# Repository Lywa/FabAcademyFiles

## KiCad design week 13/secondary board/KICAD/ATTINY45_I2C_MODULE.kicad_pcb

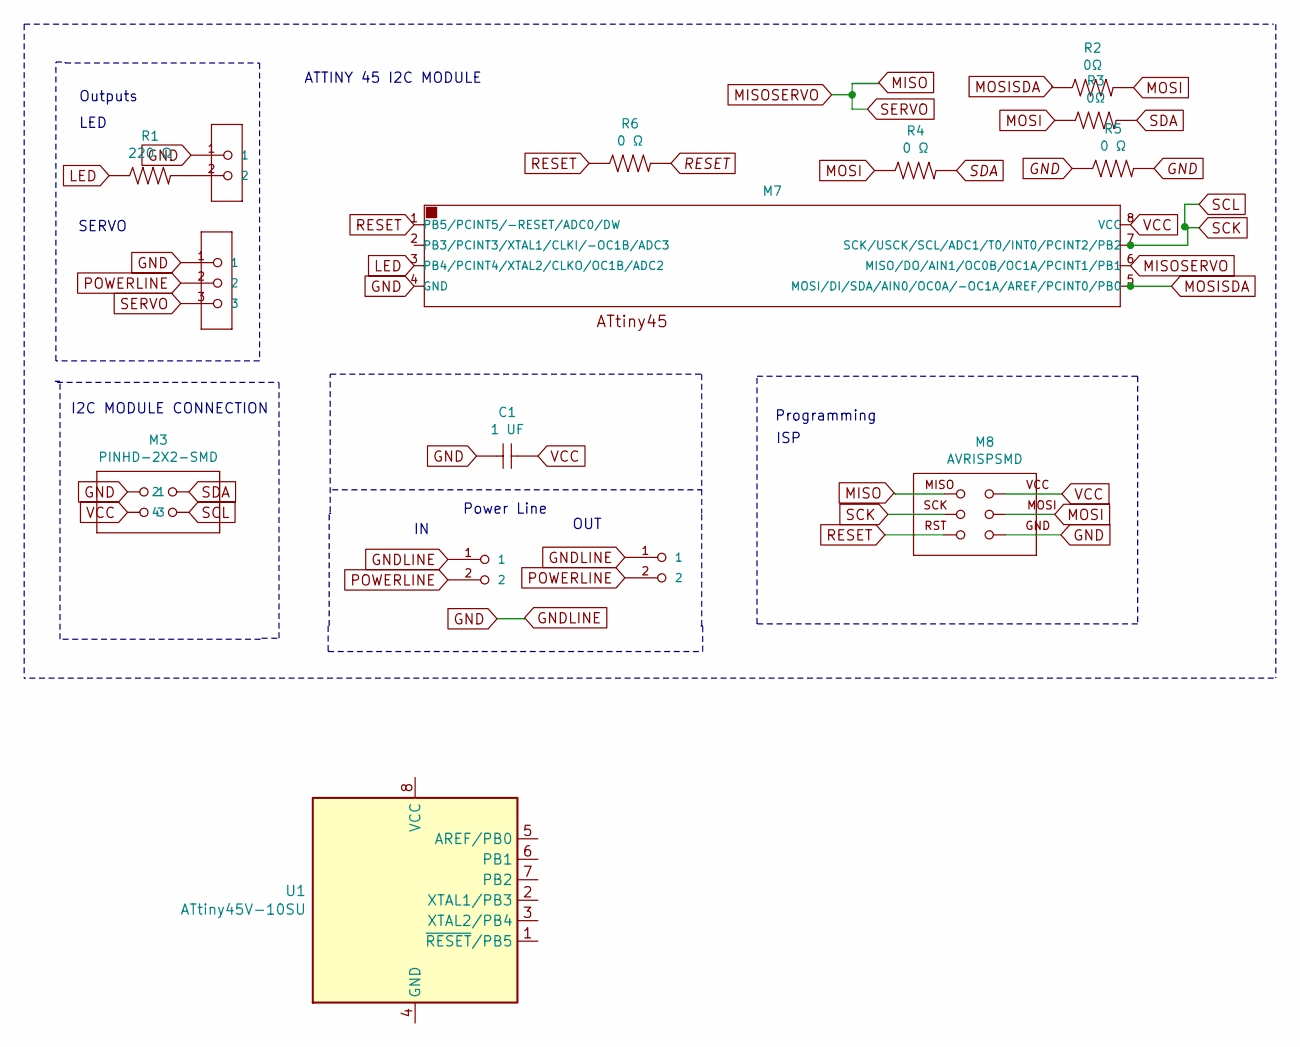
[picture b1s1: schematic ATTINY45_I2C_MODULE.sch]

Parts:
C1: 1 UF; fab-C1206
M1: PINHD-1x02-SMD-HEADER; fab-1X02SMD
M2: PINHD-1x03-SMD-HEADER; fab-1X03SMD
M3: PINHD-2X2-SMD; fab-2X02SMD
M5, M6: PINHD-1x02-HEADER; fab-1X02
M7: ATTINY45SI; fab-SOIC-8_3.9x4.9mm_P1.27mm
M8: AVRISPSMD; fab-2X03SMD
R1: 220 Ω; fab-R1206FAB
R2, R3: 0Ω; fab-R1206FAB
R4, R5, R6: 0 Ω; fab-R1206FAB
U1: ATtiny45V-10SU; SOIJ-8_5.3x5.3mm_P1.27mm

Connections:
GND: C1.1, M1.1, M2.1, M3.1, M5.1, M6.1, M7.4 (GND), M8.6 (GND), R5.1, R5.2
LED: M7.3 (PB4/PCINT4/XTAL2/CLKO/OC1B/ADC2), R1.1
MISO: M2.3, M7.6 (MISO/DO/AIN1/OC0B/OC1A/PCINT1/PB1), M8.1 (MISO)
MOSI: M8.4 (MOSI), R2.2, R3.1, R4.1
MOSISDA: M7.5 (MOSI/DI/SDA/AIN0/OC0A/-OC1A/AREF/PCINT0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), R2.1
unnamed: M1.2, R1.2
POWERLINE: M2.2, M5.2, M6.2
RESET: M7.1 (PB5/PCINT5/-RESET/ADC0/DW), M8.5 (RST), R6.1, R6.2
SCK: M3.4, M7.7 (SCK/USCK/SCL/ADC1/T0/INT0/PCINT2/PB2), M8.3 (SCK)
SDA: M3.2, R3.2, R4.2
VCC: C1.2, M3.3, M7.8 (VCC), M8.2 (VCC)

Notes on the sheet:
Programming
Outputs
Power Line
OUT
ISP
SERVO
LED
I2C MODULE CONNECTION
ATTINY 45 I2C MODULE

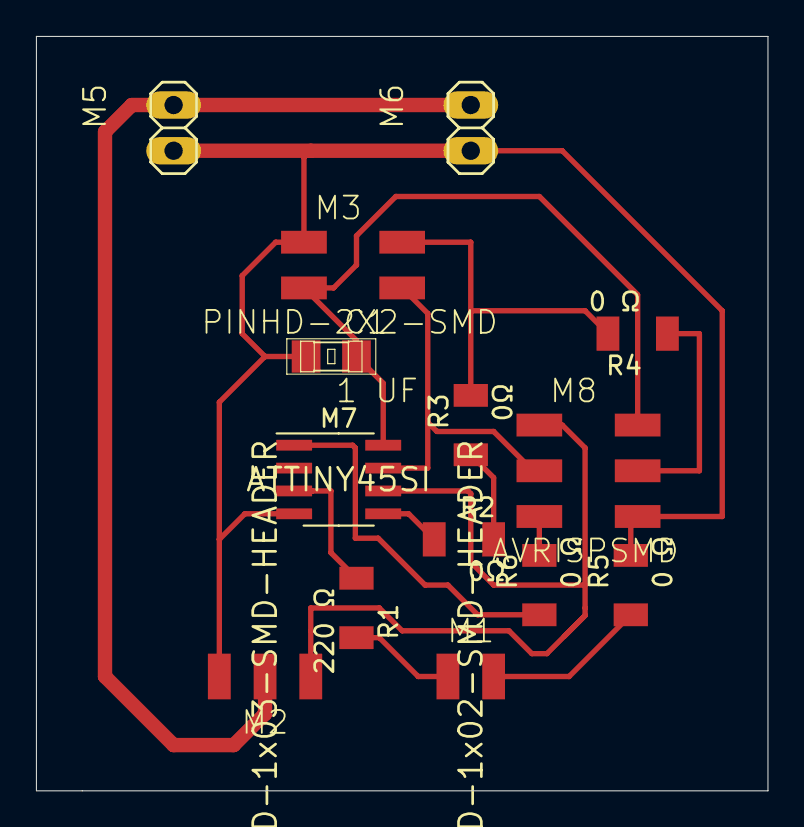
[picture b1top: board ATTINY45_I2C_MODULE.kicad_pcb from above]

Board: 2 copper layers, 40.6 x 41.9 mm, 14 parts (0 on the bottom side), 11 nets.

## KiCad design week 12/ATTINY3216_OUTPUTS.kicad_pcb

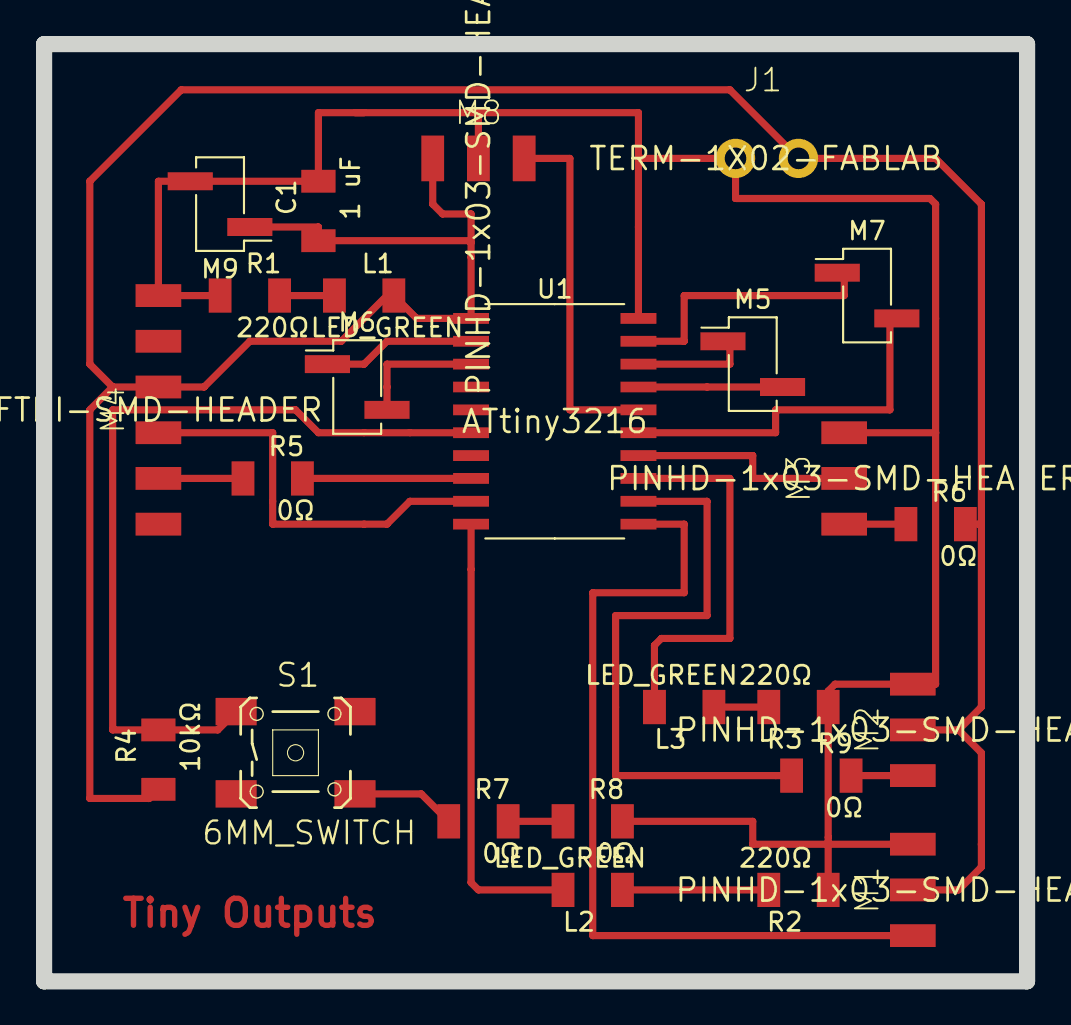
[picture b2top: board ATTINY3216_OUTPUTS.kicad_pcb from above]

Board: 2 copper layers, 54.6 x 52.1 mm, 25 parts (0 on the bottom side), 20 nets.

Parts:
C1: 1 uF; fab-C1206FAB
J1: TERM-1X02-FABLAB; fab-ED555DS-2DS
L1, L2, L3: LED_GREEN; fab-LED1206FAB
M1, M2, M3, M8: PINHD-1x03-SMD-HEADER; fab-1X03SMD
M4: FTDI-SMD-HEADER; fab-1X06SMD
M5, M6, M7, M9: PINHD-1x02-SMD-HEADER; PinHeader_1x02_P2.54mm_Vertical_SMD_Pin1Left
R1, R2, R3: 220Ω; fab-R1206FAB
R4: 10kΩ; fab-R1206FAB
R5, R6, R7, R8, R9: 0Ω; fab-R1206FAB
S1: 6MM_SWITCH; fab-6MM_SWITCH
U1: ATtiny3216; fab-SOIC-20_7.5x12.8mm_P1.27mm

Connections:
5V: C1.1, J1.1, L1.2, M1.2, M2.2, M3.3, M4.3, M8.3, M9.1, R4.1, R6.1, R6.2, U1.1
ARDUINO0: M6.1, U1.2
ARDUINO1: M6.2, U1.3
ARDUINO2: M7.1, U1.19
ARDUINO3: M7.2, U1.15
ARDUINO4: R4.2, S1.1, S1.2, U1.6
DATA12: M3.2, U1.14
GND: C1.2, J1.2, M1.1, M2.1, M3.1, M4.1, M8.2, M9.2, R1.1, R2.1, R3.1, R7.1, R7.2, R8.1, R8.2, S1.3, S1.4, U1.20
unnamed: L1.1, R1.2
unnamed: L2.1, R2.2
unnamed: L3.1, R3.2
PWM1: M1.3, U1.11
PWM2: L2.2, U1.10
PWM3: M2.3, R9.1, R9.2, U1.12
PWM4: L3.2, U1.13
RXD: M4.4, U1.9
SCL: M5.1, U1.18
SDA: M5.2, U1.17
TXD: M4.5, R5.1, R5.2, U1.8
UPDI: M8.1, U1.16

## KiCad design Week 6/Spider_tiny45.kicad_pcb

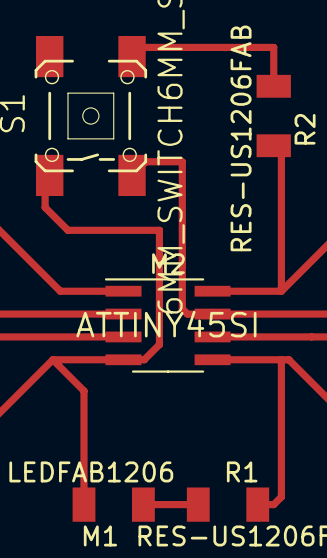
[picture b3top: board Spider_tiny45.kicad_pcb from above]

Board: 2 copper layers, 5 parts (0 on the bottom side), 6 nets.

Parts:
M1: LEDFAB1206; fab-LED1206FAB
M2: ATTINY45SI; fab-SOIC-8_3.9x4.9mm_P1.27mm
R1, R2: RES-US1206FAB; fab-R1206FAB
S1: 6MM_SWITCH6MM_SWITCH; fab-6MM_SWITCH

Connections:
7: M2.7, S1.3
GND: M1.2, M2.4, S1.1
unnamed: M1.1, R1.1
unnamed: M2.5, R1.2
unnamed: M2.8, R2.2
unnamed: R2.1, S1.4

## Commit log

2021-03-14 Week2 - Illustrator file
    Fabacademy week 2 files
2021-03-14 Week 2 Fusion Files
2021-03-14 Week 3 Files
2021-03-14 Week 3 Files update
2021-03-14 Week 4 files
2021-03-14 Week 5 files
2021-03-14 Week 5 update
2021-03-14 Week 6
2021-03-14 Week 7 files
2021-03-14 Files week 8
2021-03-22 Week 8 - Blinks
2021-04-12 Files Week 10
2021-04-13 week 9 docs
2021-04-13 Sensors 1 Day 1
2021-04-13 Sensors 1 day 2
2021-04-13 Day 3 sensors
2021-04-13 Sensors Day 4
2021-04-13 Day 5
2021-04-13 Day 6
2021-04-13 Day 7
2021-04-13 Day 8
2021-04-13 day 9
2021-04-13 day 10
2021-04-14 Day 11 sensors
2021-04-14 Day 12 sensors
2021-04-14 Day 15
2021-04-14 Day 16
2021-04-14 day 17&18
2021-04-14 machine design
2021-04-20 week 11 files
2021-04-20 week 11 update
2021-04-20 update week 11
2021-04-26 Week 12 files
2021-05-05 Final Project Gear Box v1
2021-05-05 i2c workshop files
2021-05-05 pcb files
2021-05-05 week 13 code
2021-05-11 week 14 files
2021-06-16 final code working I2C boards
2021-06-22 Cnc pdf
2021-07-03 Final Project Large Files
